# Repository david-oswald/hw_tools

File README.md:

# hw_tools
Collection of various smallish hardware tools (adapter PCBs, processor boards, etc)

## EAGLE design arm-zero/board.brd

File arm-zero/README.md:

# STM32F405 board in Raspberry Pi Zero form factor

STM32F405RGT6 (LQFP64) microcontroller board in the form factor of a RPi Zero. 

## Features

 - STM32F4xx MCU with 1 MB flash, 192 kB SRAM, USB 2.0, max. 168 MHz clock
 - Projects can use existing cases for RPi Zero
 - Programmable via bootloader (button) or programmer (SWD interface)
 - Powered from USB
 - Power LED + 2 user-defined LEDs
 - A few pins (not all) broken out to RPi connector
 - Power pins (GND, 3V3, *not* 5V) are assigned to correct RPi connector pins
 - Could be theoretically used as an add-on board for RPi zero, this is
   however *not* tested. Feel free to test and improve pin mapping.
 - 2 layer board, fairly standard / cheap components, most expensive part is
   [STM32F405RGT6](http://www.st.com/content/st_com/en/products/microcontrollers/stm32-32-bit-arm-cortex-mcus/stm32f4-series/stm32f405-415/stm32f405rg.html)
   at approx. 10 USD in small quantities
 - Easy to solder (LQFP, 0603 components)

## Mapped pins

 - PD2 -> GPIO17
 - PC12 -> GPIO18
 - PC10 -> GPIO22
 - PA15 -> GPIO23
 - PC11 -> GPIO27
 
## Todo
  
  - Provide example code
  - Pin mapping to work as RPi extension
  - Break out all remaining STM32F405 pins

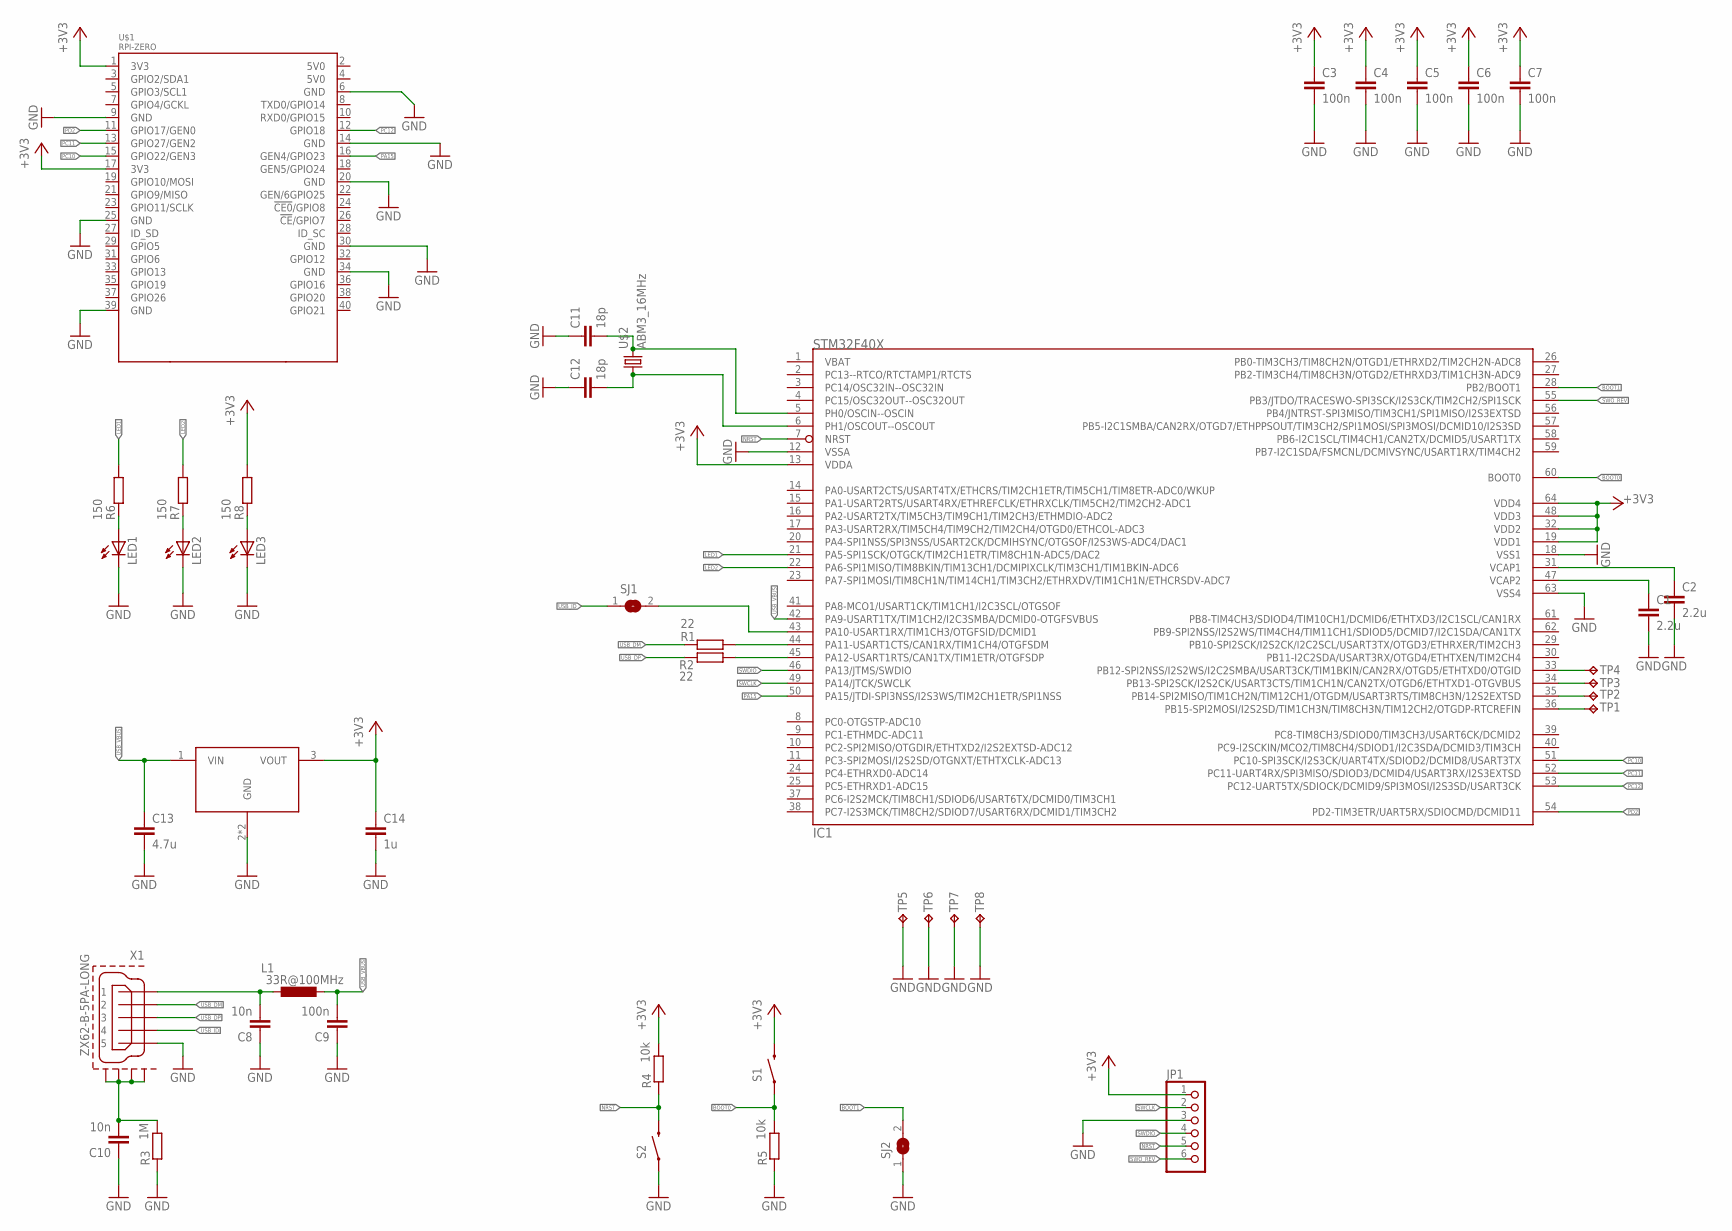
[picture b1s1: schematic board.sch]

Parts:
C1, C2: 2.2u; C0805
C3, C4, C5, C6, C7, C9: 100n; C0603
C8, C10: 10n; C0603
C11, C12: 18p; C0603
C13: 4.7u; C0805
C14: 1u; C0805
IC1: STM32F40X; LQFP64
JP1: PINHD-1X6; 1X06
L1: 33R@100MHz; L2012C
LED1, LED2, LED3: LEDCHIPLED_0805; CHIPLED_0805
R1, R2: 22; R0603
R3: 1M; R0603
R4, R5: 10k; R0603
R6, R7, R8: 150; R0603
S1, S2: SWITCH-MOMENTARY-2SMD; TACTILE-SWITCH-SMD
SJ1, SJ2: SJ
TP1, TP2, TP3, TP4, TP5, TP6, TP7, TP8: TPB1,27; B1,27
U$1: RPI-ZERO; RASPBERRYPI_BASTELSTUBE_V13_RASPI_BOARD_B+_FULL
U$2: ABM3_16MHz; ABRACON_ABM3_CRYSTAL
U$3: MCP1825; SOT223-3
X1: ZX62-B-5PA-LONG

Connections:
+3V3: C3.1, C4.1, C5.1, C6.1, C7.1, C14.1, IC1.13 (VDDA), IC1.19 (VDD1), IC1.32 (VDD2), IC1.48 (VDD3), IC1.64 (VDD4), JP1.1, R4.2, R8.2, S1.3 (2), U$1.1 (3V3), U$1.17 (3V3), U$3.3 (VOUT)
BOOT0: IC1.60 (BOOT0), R5.2, S1.1
BOOT1: IC1.28 (PB2/BOOT1), SJ2.2
GND: C1.2, C2.2, C3.2, C4.2, C5.2, C6.2, C7.2, C8.1, C9.1, C10.1, C11.1, C12.1, C13.2, C14.2, IC1.12 (VSSA), IC1.18 (VSS1), IC1.63 (VSS4), JP1.3, LED1.C, LED2.C, LED3.C, R3.1, R5.1, S2.1, SJ2.1, TP5.TP, TP6.TP, TP7.TP, TP8.TP, U$1.6 (GND), U$1.9 (GND), U$1.14 (GND), U$1.20 (GND), U$1.25 (GND), U$1.30 (GND), U$1.34 (GND), U$1.39 (GND), U$3.2 (GND), U$3.4 (GND), X1.5
LED1: IC1.21 (PA5-SPI1SCK/OTGCK/TIM2CH1ETR/TIM8CH1N-A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), R6.2
LED2: IC1.22 (PA6-SPI1MISO/TIM8BKIN/TIM13CH1/DCMIPIXC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), R7.2
unnamed: C8.2, L1.1, X1.1
unnamed: C10.2, R3.2, X1.P$1 (GND1), X1.P$2 (GND2), X1.P$5 (GND4), X1.P$6 (GND3)
unnamed: IC1.44 (PA11-USART1CTS/CAN1RX/TIM1CH4/OTGFSDM), R1.2
unnamed: IC1.45 (PA12-USART1RTS/CAN1TX/TIM1ETR/OTGFSDP), R2.2
unnamed: IC1.43 (PA10-USART1RX/TIM1CH3/OTGFSID/DCMID1), SJ1.2
unnamed: LED1.A, R6.1
unnamed: C12.2, IC1.6 (PH1/OSCOUT--OSCOUT), U$2.P$1 (1)
unnamed: C11.2, IC1.5 (PH0/OSCIN--OSCIN), U$2.P$2 (2)
unnamed: LED2.A, R7.1
unnamed: LED3.A, R8.1
unnamed: IC1.36 (PB15-SPI2MOSI/I2S2SD/TIM1CH3N/TIM8CH3N/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), TP1.TP
unnamed: IC1.35 (PB14-SPI2MISO/TIM1CH2N/TIM12CH1/OTGDM/U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), TP2.TP
unnamed: IC1.34 (PB13-SPI2SCK/I2S2CK/USART3CTS/TIM1CH1N/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), TP3.TP
unnamed: IC1.33 (PB12-SPI2NSS/I2S2WS/I2C2SMBA/USART3CK/T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), TP4.TP
NRST: IC1.7 (NRST), JP1.5, R4.1, S2.3 (2)
PA15: IC1.50 (PA15/JTDI-SPI3NSS/I2S3WS/TIM2CH1ETR/SPI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), U$1.16 (GEN4/GPIO23)
PC10: IC1.51 (PC10-SPI3SCK/I2S3CK/UART4TX/SDIOD2/DCMI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), U$1.15 (GPIO22/GEN3)
PC11: IC1.52 (PC11-UART4RX/SPI3MISO/SDIOD3/DCMID4/USA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), U$1.13 (GPIO27/GEN2)
PC12: IC1.53 (PC12-UART5TX/SDIOCK/DCMID9/SPI3MOSI/I2S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), U$1.12 (GPIO18)
PD2: IC1.54 (PD2-TIM3ETR/UART5RX/SDIOCMD/DCMID11), U$1.11 (GPIO17/GEN0)
SWCLK: IC1.49 (PA14/JTCK/SWCLK), JP1.2
SWDIO: IC1.46 (PA13/JTMS/SWDIO), JP1.4
SWO_REV: IC1.55 (PB3/JTDO/TRACESWO-SPI3SCK/I2S3CK/TIM2CH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), JP1.6
USB_DM: R1.1, X1.2
USB_DP: R2.1, X1.3
USB_ID: SJ1.1, X1.4
USB_VBUS: C9.2, C13.1, IC1.42 (PA9-USART1TX/TIM1CH2/I2C3SMBA/DCMID0-OT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), L1.2, U$3.1 (VIN)
VCAP1: C2.1, IC1.31 (VCAP1)
VCAP2: C1.1, IC1.47 (VCAP2)

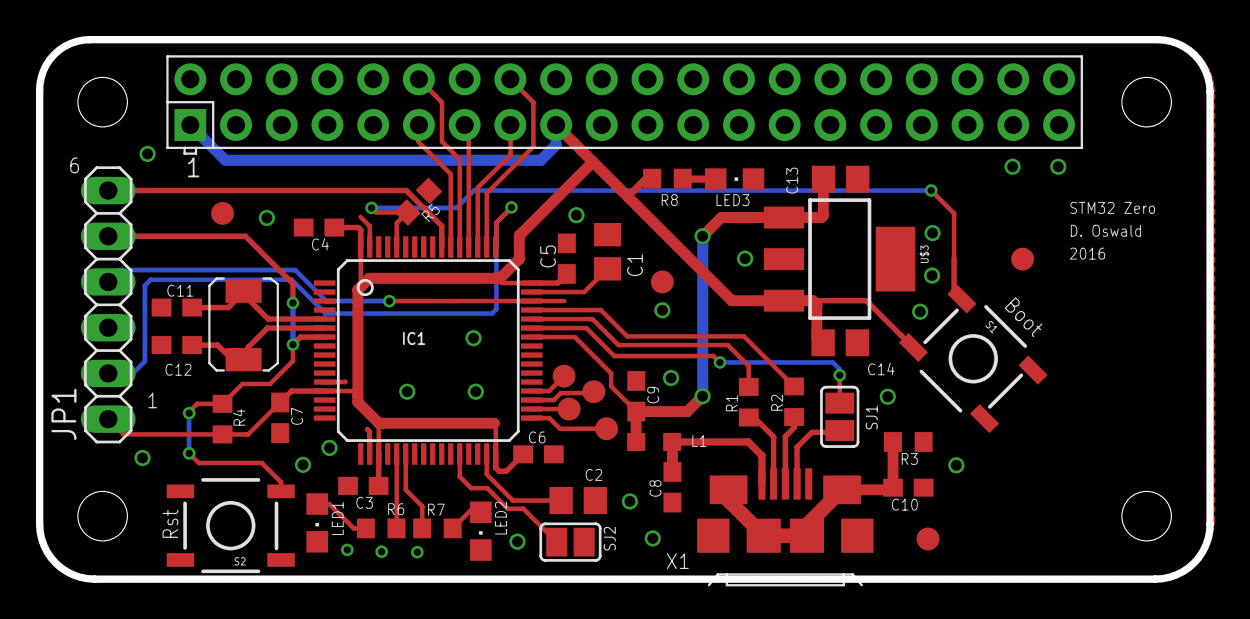
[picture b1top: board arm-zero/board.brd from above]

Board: 2 copper layers, 65.0 x 30.0 mm, 44 parts (0 on the bottom side), 35 nets.

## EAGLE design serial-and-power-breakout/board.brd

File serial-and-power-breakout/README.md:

# USB / Voltage breakout board

Provides a USB-to-UART interface using an FT230X. In addition, has a LM317
to provide a potentiometer-set output voltage. The IO voltage of the FT230X
can be jumper-configured to either use the voltage from the FTDI chip
(3.3 V, max. 50 mA) or the LM317 output (min. 100 mA, typ. 200 mA).

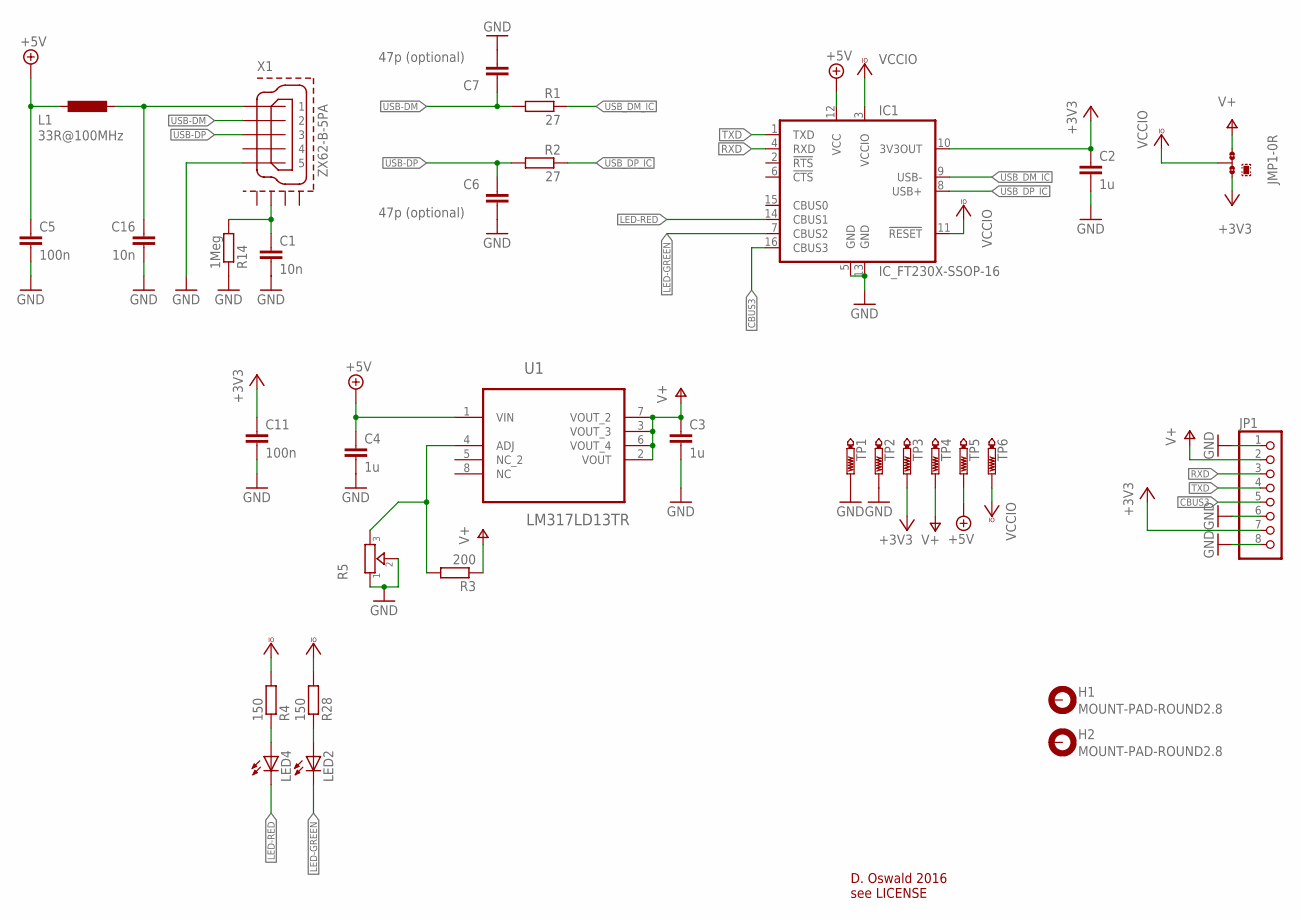
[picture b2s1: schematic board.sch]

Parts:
C1, C16: 10n; C0603K
C2, C3, C4: 1u; C0805K
C5, C11: 100n; C0603K
C6, C7: 47p (optional); C0603K
H1, H2: MOUNT-PAD-ROUND2.8; 2,8-PAD
IC1: IC_FT230X-SSOP-16; SSOP-16-FTDI
JMP1: 0R-JUMPA; A0R-JMP
JP1: PINHD-1X8/90; 1X08/90
L1: 33R@100MHz; L2012C
LED2, LED4: LEDCHIPLED_0805; CHIPLED_0805
R1, R2: 27; R0603
R3: 200; R0805
R4, R28: 150; R0603
R5: TRIMMER-3314G; TRIMMER_3314G
R14: 1Meg; R0603
TP1, TP2, TP3, TP4, TP5, TP6: PTR1B1,27; B1,27
U1: LM317LD13TR; SOIC127P600X175-8N
X1: ZX62-B-5PA; ZX62-B-5PA-LONG

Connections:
+3V3: C2.1, C11.1, IC1.10 (3V3OUT), JMP1.1, JP1.7, TP3.TP
+5V: C4.1, C5.1, IC1.12 (VCC), L1.2, TP5.TP, U1.1 (VIN)
CBUS3: IC1.16 (CBUS3), JP1.5
GND: C1.2, C2.2, C3.2, C4.2, C5.2, C6.2, C7.1, C11.2, C16.2, IC1.5 (GND), IC1.13 (GND), JP1.1, JP1.6, JP1.8, R5.1, R5.2, R14.1, TP1.TP, TP2.TP, X1.5
LED-GREEN: IC1.7 (CBUS2), LED2.C
LED-RED: IC1.14 (CBUS1), LED4.C
unnamed: R3.2, R5.3, U1.4 (ADJ)
unnamed: LED2.A, R28.1
unnamed: LED4.A, R4.1
unnamed: C16.1, L1.1, X1.1
unnamed: C1.1, R14.2, X1.P$2 (GND2)
RXD: IC1.4 (RXD), JP1.3
TXD: IC1.1 (TXD), JP1.4
USB-DM: C7.2, R1.2, X1.2
USB-DP: C6.1, R2.2, X1.3
USB_DM_IC: IC1.9 (USB-), R1.1
USB_DP_IC: IC1.8 (USB+), R2.1
V+: C3.1, JMP1.3, JP1.2, R3.1, TP4.TP, U1.2 (VOUT), U1.3 (VOUT_3), U1.6 (VOUT_4), U1.7 (VOUT_2)
VCCIO: IC1.3 (VCCIO), IC1.11 (!RESET), JMP1.2, R4.2, R28.2, TP6.TP

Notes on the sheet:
D. Oswald 2016 see LICENSE

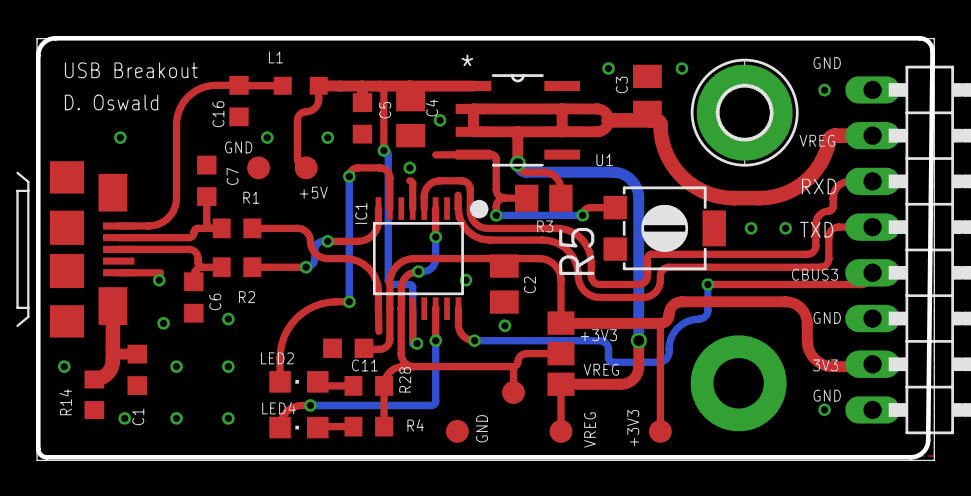
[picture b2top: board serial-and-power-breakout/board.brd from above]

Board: 2 copper layers, 49.7 x 23.3 mm, 32 parts (1 on the bottom side), 19 nets.

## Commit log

2016-06-08 Created readme
2016-06-08 Initial commit of EAGLE files, PDF, BOM, README
2016-09-12 arm-zero board / schematic with README

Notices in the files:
parts and their libraries:
SparkFun-Electromechanical: Licensing: Creative Commons ShareAlike 4.0 International - https://creativecommons.org/licenses/by-sa/4.0
